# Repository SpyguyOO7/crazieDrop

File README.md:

# PCB for little electromagnet drop mech
## SChematic

## Model + Layout

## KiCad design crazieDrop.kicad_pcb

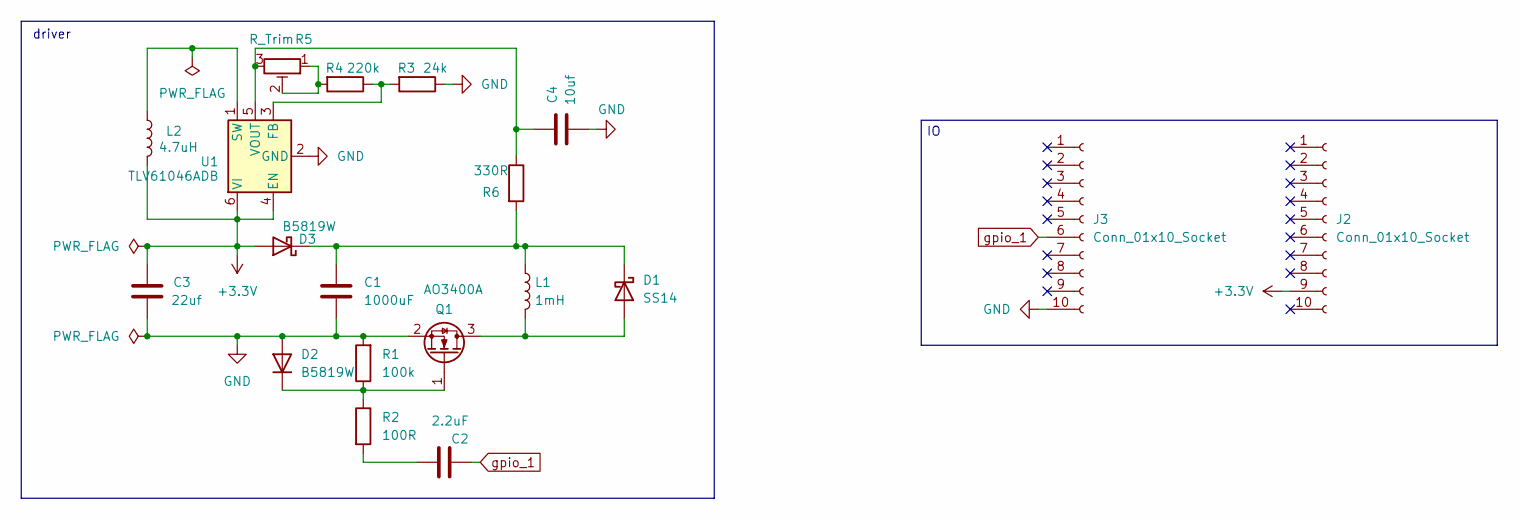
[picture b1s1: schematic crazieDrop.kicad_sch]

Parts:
C1: 1000uF; CP_Radial_D10.0mm_P5.00mm
C2: 2.2uF; C_0603_1608Metric; LCSC C23630
C3: 22uf; C_0805_2012Metric_Pad1.18x1.45mm_HandSolder; LCSC C45783
C4: 10uf; C_0805_2012Metric_Pad1.18x1.45mm_HandSolder; LCSC C440198
D1: SS14; D_SMA_Handsoldering; LCSC C2480
D2, D3: B5819W; D_SOD-123; LCSC C8598
J2, J3: Conn_01x10_Socket; PinSocket_1x10_P2.00mm_Vertical_SMD_Pin1Right
L1: 1mH; PinHeader_1x02_P2.54mm_Vertical
L2: 4.7uH; L_Vishay_IFSC-1515AH_4x4x1.8mm; LCSC C354574
Q1: AO3400A; SOT-23_Handsoldering; LCSC C20917
R1: 100k; R_0603_1608Metric; LCSC C25803
R2: 100R; R_0603_1608Metric; LCSC C22775
R3: 24k; R_0603_1608Metric_Pad0.98x0.95mm_HandSolder; LCSC C23352
R4: 220k; R_0603_1608Metric_Pad0.98x0.95mm_HandSolder; LCSC C22961
R5: R_Trim; Potentiometer_Bourns_3314J_Vertical; LCSC C56560
R6: 330R; R_0805_2012Metric_Pad1.20x1.40mm_HandSolder; LCSC C17630
U1: TLV61046ADB; SOT-23-6; LCSC C464815

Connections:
+3.3V: C3.1, D3.2 (A), J2.9 (Pin_9_9), L2.2, U1.4 (EN), U1.6 (VI)
GND: C1.2, C3.2, C4.2, D2.2 (A), J3.10, Q1.2 (S), R1.2, R3.1, U1.2 (GND)
unnamed: C2.1, R2.2
unnamed: D1.2 (A), L1.2, Q1.3 (D)
unnamed: C1.1, D1.1 (K), D3.1 (K), L1.1, R6.2
unnamed: D2.1 (K), Q1.1 (G), R1.1, R2.1
unnamed: R4.2, R5.1, R5.2
unnamed: R3.2, R4.1, U1.3 (FB)
unnamed: L2.1, U1.1 (SW)
unnamed: C4.1, R5.3, R6.1, U1.5 (VOUT)
gpio_1: C2.2, J3.6

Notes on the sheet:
driver

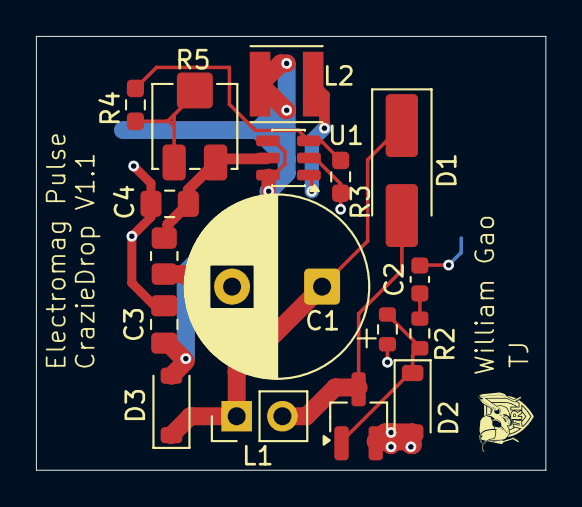
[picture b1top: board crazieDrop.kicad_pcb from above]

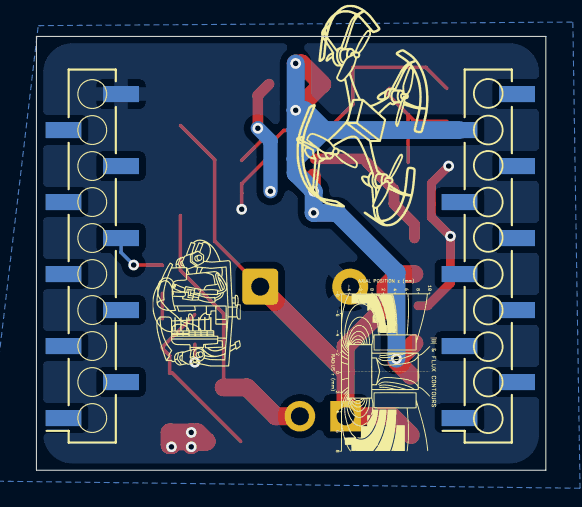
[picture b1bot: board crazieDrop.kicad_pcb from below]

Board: 2 copper layers, 28.3 x 24.1 mm, 19 parts (2 on the bottom side), 11 nets.

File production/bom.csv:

Designator,Footprint,Quantity,Value,LCSC Part #
BT1,PinHeader_1x02_P2.54mm_Vertical,1,Battery,
C1,CP_Radial_D10.0mm_P5.00mm,1,1000uF,
C2,0603,1,2.2uF,C23630
C3,0805,1,22uf,C45783
C4,0805,1,10uf,C440198
D1,D_SMA_Handsoldering,1,SS14,C2480
"D2, D3",D_SOD-123,2,B5819W,C8598
J1,PinHeader_1x01_P2.54mm_Vertical,1,control_gpio,
L1,PinHeader_1x02_P2.54mm_Vertical,1,1mH,
L2,L_Vishay_IFSC-1515AH_4x4x1.8mm,1,4.7uH,C354574
Q1,SOT-23_Handsoldering,1,AO3400A,C20917
R1,0603,1,100k,C25803
R2,0603,1,100R,C22775
R3,0603,1,24k,C23352
R4,0603,1,220k,C22961
R5,Potentiometer_Bourns_3314J_Vertical,1,R_Trim,C56560
R6,0805,1,330R,C17630
U1,SOT-23-6,1,TLV61046ADB,C464815
